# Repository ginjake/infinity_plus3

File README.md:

# これはなに？
自作キーボード `infinity_plus3` 
の基板とケースのデータです。

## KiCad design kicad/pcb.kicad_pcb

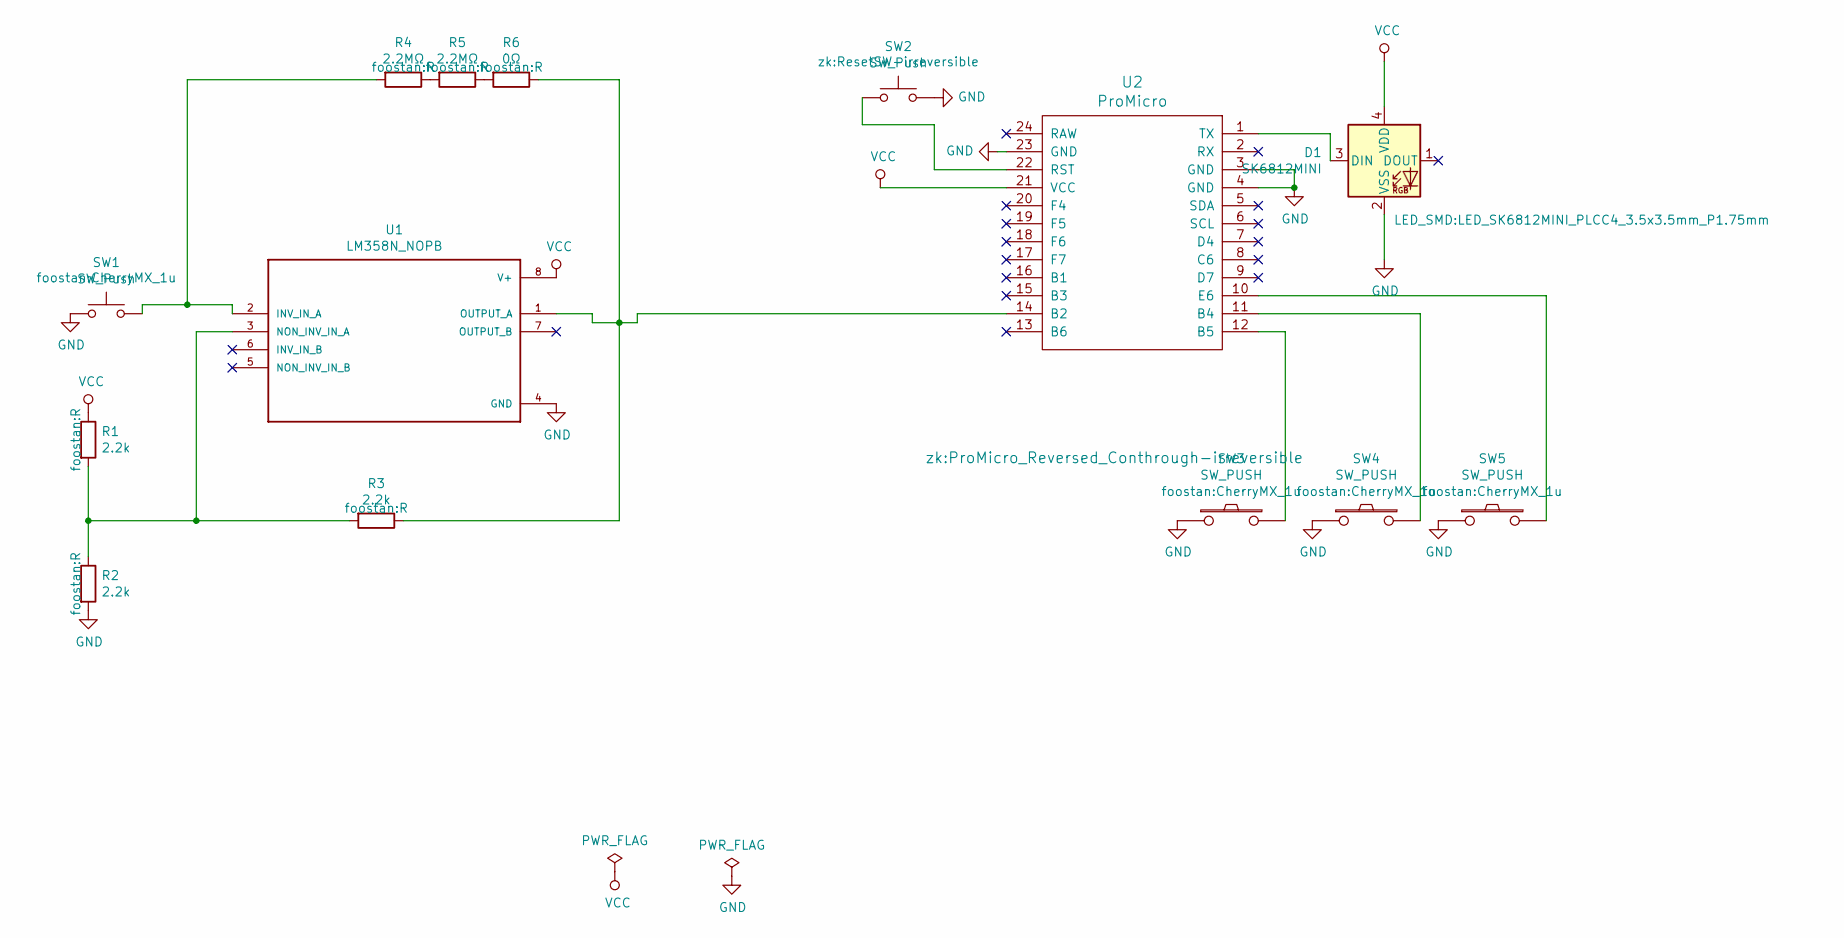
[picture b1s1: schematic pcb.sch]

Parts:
D1: SK6812MINI; LED_SK6812MINI_PLCC4_3.5x3.5mm_P1.75mm
R1, R2, R3: 2.2k; R
R4, R5: 2.2MΩ; R
R6: 0Ω; R
SW1: SW_Push; CherryMX_1u
SW2: SW_Push; ResetSW-irreversible
SW3, SW4, SW5: SW_PUSH; CherryMX_1u
U1: LM358N_NOPB; DIP-8_W7.62mm
U2: ProMicro; ProMicro_Reversed_Conthrough-irreversible

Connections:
GND: D1.2 (VSS), R2.2, SW1.1, SW2.2, SW3.1, SW4.1, SW5.1, U1.4 (GND), U2.3 (GND), U2.4 (GND), U2.23 (GND)
unnamed: D1.3 (DIN), U2.1 (TX)
unnamed: R1.2, R2.1, R3.2, U1.3 (NON_INV_IN_A)
unnamed: R3.1, R6.1, U1.1 (OUTPUT_A), U2.14 (B2)
unnamed: R4.1, R5.2
unnamed: R4.2, SW1.2, U1.2 (INV_IN_A)
unnamed: R5.1, R6.2
unnamed: SW2.1, U2.22 (RST)
unnamed: SW3.2, U2.12 (B5)
unnamed: SW4.2, U2.11 (B4)
unnamed: SW5.2, U2.10 (E6)
VCC: D1.4 (VDD), R1.1, U1.8 (V+), U2.21 (VCC)

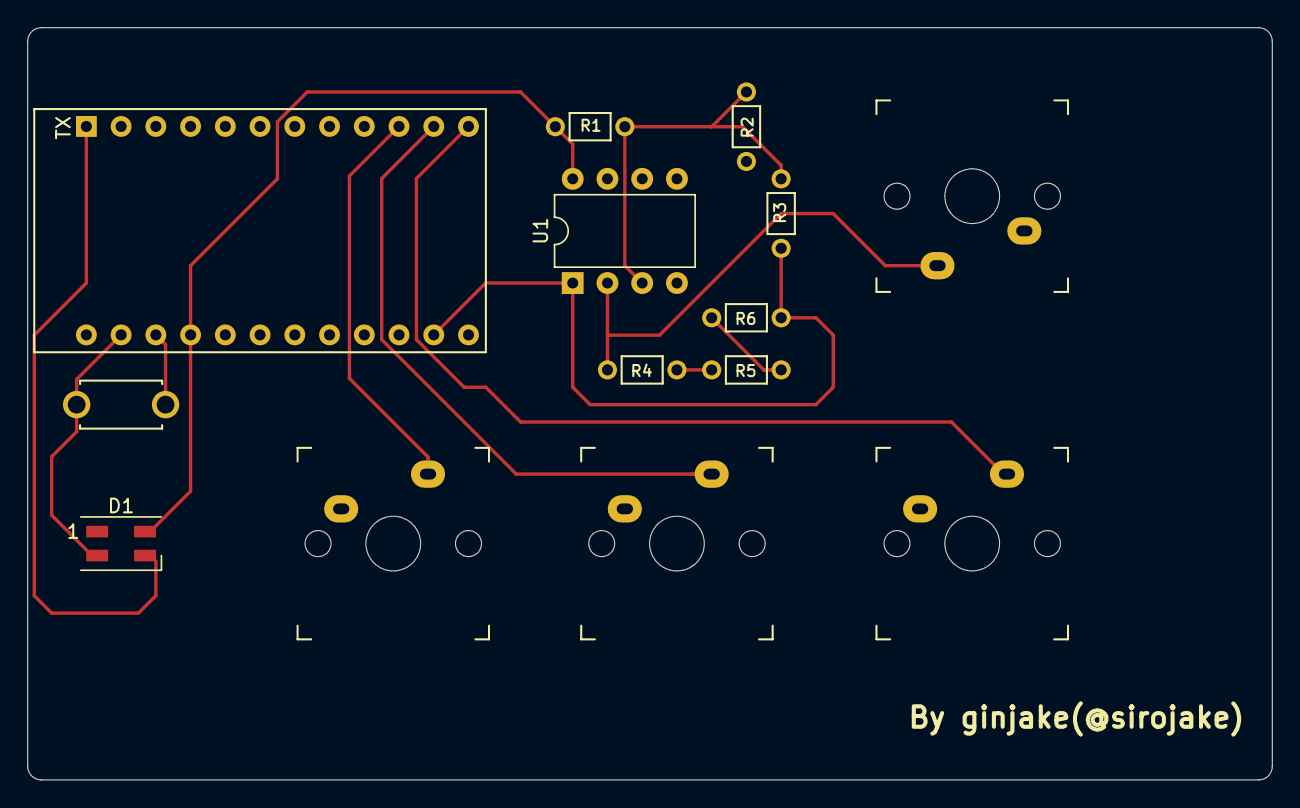
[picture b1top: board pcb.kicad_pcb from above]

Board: 2 copper layers, 91.0 x 55.0 mm, 14 parts (0 on the bottom side), 12 nets.

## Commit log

2019-05-20 kicad追加
2019-05-20 ケース再アップ
